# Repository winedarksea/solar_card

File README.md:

# Solar-Powered LED Flashlight Business Card
created by Colin Catlin, 2023

A business card that can also double as a decently powerful, RGB flashlight, complete with solar charging. Built for business, ready for the apocalypse.

Built in KiCAD V6, opens with V7 and possibly later (those haven't been released as of this release).

GPLv3 licensed so that you can freely go and make variations with your own name. Or run around handling out ones with my name while pretending to be me? Please only do the latter if you are very charming and attractive.

I have had this made and assembled by JLCPCB, as you'll notice. Only the back side was assembled by them. 
Additionally there is a PTC reset fuse which is marked with a 0 ohm resistor, size 1812. 
You can use the resistor if you don't want the reset fuse, it isn't necessary but adds a little extra safety.

For that fuse, I chose Bourns MF-MSMF020-2 PTC RESET FUSE 30V 200MA 1812 and hand-assembled it with hot air. It's a relatively big part, easy to solder.

I also hand assembled the solar panel and the LEDs on the front side. Choosing LEDs is fun. I tried to size the pad so that that most 3030 or 2835 LEDs would work. 
I found that it even works with those that have a three part footprint (one of which can safely be connected to return). 

The giant vias are for allowing hot air from the bottom to reach solder paste on the other side for attaching the solar panel. It works. Actually these vias are bigger than really necessary, going down a bit smaller would work well and be more discrete, but not too small, 0.3 mm was definitely too small.

The idea here with three LEDs is that you can choose three different colors, red, green, and blue, and then mix them with potentiometers to make 'any' color. It works! 
But for more flashlight purposes you can just choose the most efficient white-ish colors (for still some fun, choose a low kelvin and high kelvin color mix, so you still can get blue-ish and yellow-ish). I had thought the Samsung ultra efficient LEDs would be best, and they do work well, but for the best flashlight I found the narrowest possible viewing angle made the most impact (since there is no light focusing reflector here like a normal flashlight). One I tried that worked well was the "LED Lighting OSLON® SSL 80 White, Cool 6500K 2.85V 350mA 80° 1212 (3030 Metric)" - the most important part is that 80 degree viewing angle.

The idea here was the undervoltage protection would be afforded by the dropout voltage of the LEDs (they stop working with too little voltage, that's good here). Unfortunately I have found that green LEDs, in particular, can run down to a lower voltage than their datasheet suggests. Check the minimum voltage of LEDs manually if aiming for optimal battery protection.

Please see my blogpost for more details: 
https://syllepsis.live/2023/08/05/the-solar-powered-business-card/

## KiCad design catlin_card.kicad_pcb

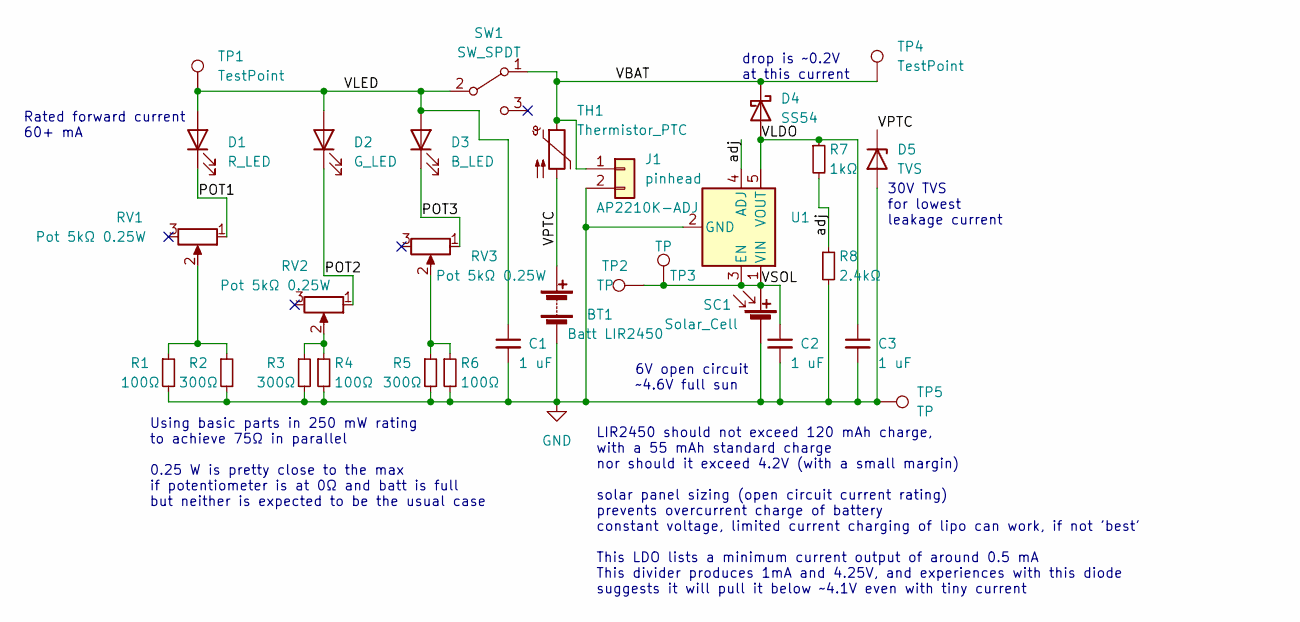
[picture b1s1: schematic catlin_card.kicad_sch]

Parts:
BT1: Batt LIR2450; BatteryHolder_Keystone_3008_1x2450
C1, C2, C3: 1 uF; C_0805_2012Metric_Pad1.18x1.45mm_HandSolder
D1: R_LED; LED_SMD3030
D2: G_LED; LED_SMD3030
D3: B_LED; LED_SMD3030
D4: SS54; D_SMA_Handsoldering
D5: TVS; D_SOD-123
J1: pinhead; PinHeader_1x02_P2.54mm_Vertical
R1, R4, R6: 100Ω; R_1206_3216Metric
R2, R3, R5: 300Ω; R_1206_3216Metric
R7: 1kΩ; R_0805_2012Metric_Pad1.20x1.40mm_HandSolder
R8: 2.4kΩ; R_0805_2012Metric_Pad1.20x1.40mm_HandSolder
RV1, RV2, RV3: Pot 5kΩ 0.25W; Potentiometer_Bourns_3314G_Vertical
SC1: Solar_Cell; R_4020_10251Metric
SW1: SW_SPDT; SW_SPDT_PCM12
TH1: Thermistor_PTC; R_1812_4532Metric_Pad1.30x3.40mm_HandSolder
TP1, TP4: TestPoint; TestPoint_Pad_2.0x2.0mm
TP2, TP5: TP; TestPoint_Pad_4.0x4.0mm
TP3: TP; TestPoint_Pad_1.0x1.0mm
U1: AP2210K-ADJ; SOT-23-5

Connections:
/POT1: D1.1 (K), RV1.1
/POT2: D2.1 (K), RV2.1
/POT3: D3.1 (K), RV3.1
/VBAT: D4.1 (K), J1.1, SW1.1 (A), TH1.1, TP4.1
/VLDO: C3.1, D4.2 (A), R7.1, U1.5 (VOUT)
/VLED: C1.1, D1.2 (A), D2.2 (A), D3.2 (A), SW1.2 (B), TP1.1
/VPTC: BT1.1 (+), D5.1 (K), TH1.2
/VSOL: C2.1, SC1.1 (+), TP2.1, TP3.1, U1.1 (VIN), U1.3 (EN)
/adj: R7.2, R8.1, U1.4 (ADJ)
GND: BT1.2 (-), C1.2, C2.2, C3.2, D5.2 (A), J1.2, R1.2, R2.2, R3.2, R4.2, R5.2, R6.2, R8.2, SC1.2 (-), TP5.1, U1.2 (GND)
unnamed: R1.1, R2.1, RV1.2
unnamed: R3.1, R4.1, RV2.2
unnamed: R5.1, R6.1, RV3.2

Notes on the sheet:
Rated forward current 60+ mA
LIR2450 should not exceed 120 mAh charge, with a 55 mAh standard charge nor should it exceed 4.2V (with a small margin) solar panel sizing (open circuit current rating) prevents overcurrent charge of battery constant voltage, limited current charging of lipo can work, if not 'best' This LDO lists a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
6V open circuit ~4.6V full sun
30V TVS for lowest leakage current
Using basic parts in 250 mW rating to achieve 75Ω in parallel 0.25 W is pretty close to the max if potentiometer is at 0Ω and batt is full but neither is expected to be the usual case
drop is ~0.2V at this current

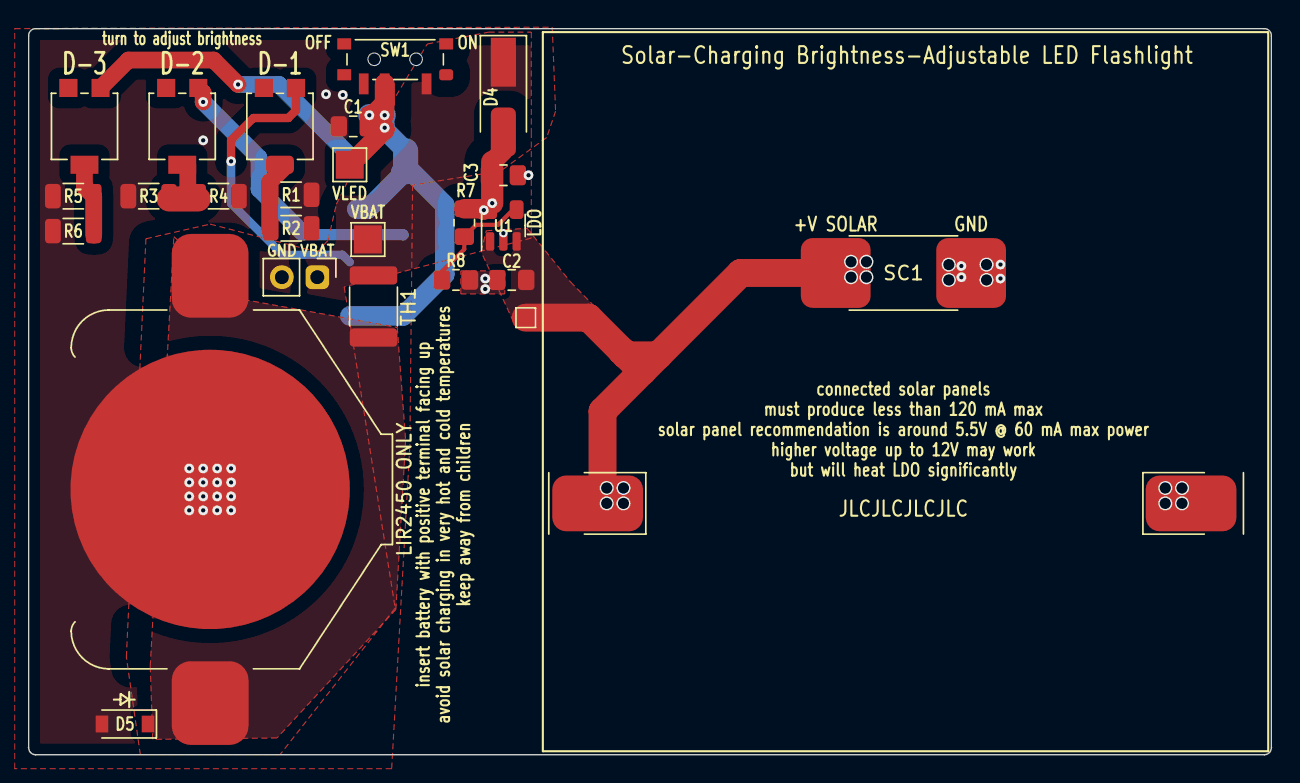
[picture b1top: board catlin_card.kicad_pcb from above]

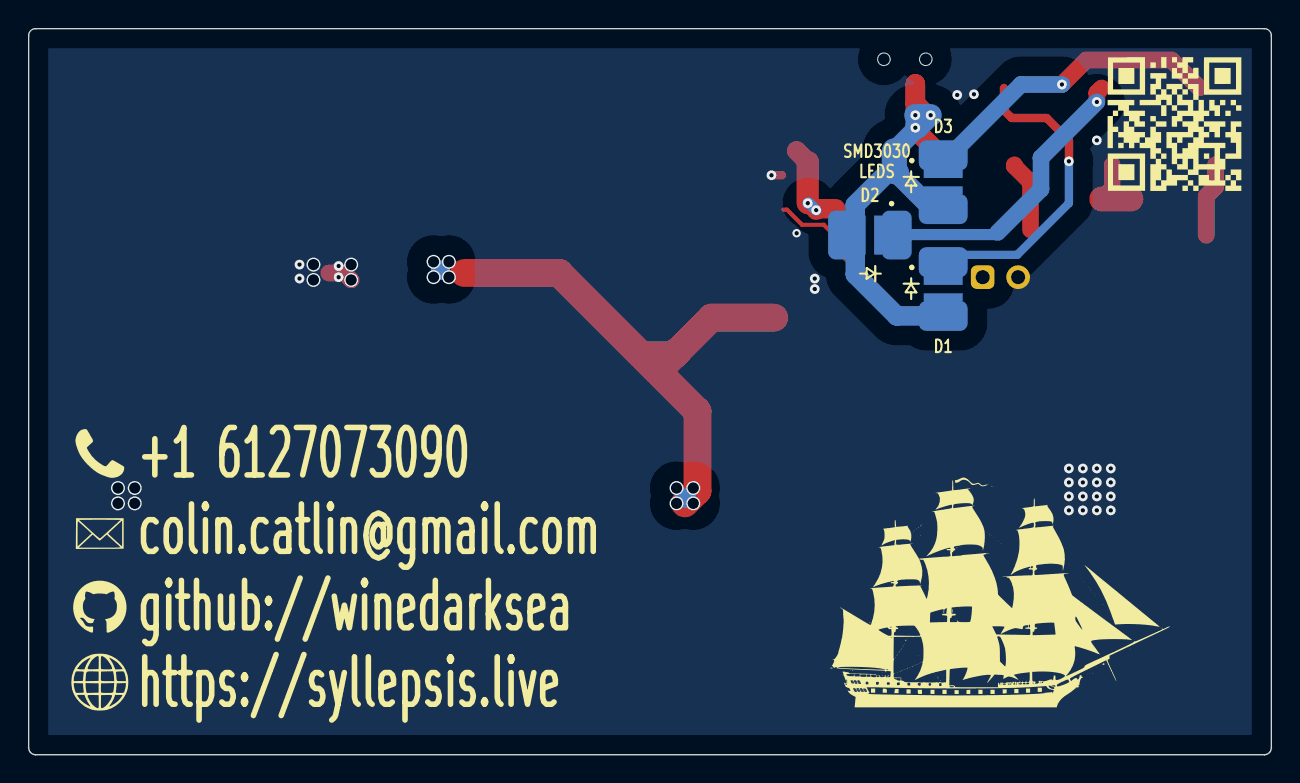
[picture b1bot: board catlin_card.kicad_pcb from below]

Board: 2 copper layers, 89.0 x 52.0 mm, 30 parts (3 on the bottom side), 13 nets.

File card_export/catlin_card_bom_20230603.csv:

Designator,Comment,Footprint,JCLPCB Part #
"BT1,",Batt LIR2450,Battery:BatteryHolder_Keystone_3008_1x2450,C964845
"C1, C2, C3,",1 uF,Capacitor_SMD:C_0805_2012Metric_Pad1.18x1.45mm_HandSolder,C28323
"D1,",R_LED,PowerIC:LED_SMD3030,C1322324
"D2,",G_LED,PowerIC:LED_SMD3030,C1322325
"D3,",B_LED,PowerIC:LED_SMD3030,C440449
"D4,",SS54,Diode_SMD:D_SMA_Handsoldering,C22452
"D5,",TVS,Diode_SMD:D_SOD-123,C2990493
"J1,",pinhead,Connector_PinHeader_2.54mm:PinHeader_1x02_P2.54mm_Vertical,
"R1, R4, R6,",100Ω,Resistor_SMD:R_1206_3216Metric,C17901
"R2, R3, R5,",300Ω,Resistor_SMD:R_1206_3216Metric,C17887
"R7,",1kΩ,Resistor_SMD:R_0805_2012Metric_Pad1.20x1.40mm_HandSolder,C17513
"R8,",2.4kΩ,Resistor_SMD:R_0805_2012Metric_Pad1.20x1.40mm_HandSolder,C17526
"RV1, RV2, RV3,",Pot 5kΩ 0.25W,Potentiometer_SMD:Potentiometer_Bourns_3314G_Vertical,C719180
"SC1,",Solar_Cell,Resistor_SMD:R_4020_10251Metric,SM141K10LV
"SW1,",SW_SPDT,Button_Switch_SMD:SW_SPDT_PCM12,C128955
"TH1,",Thermistor_PTC,Resistor_SMD:R_1812_4532Metric_Pad1.30x3.40mm_HandSolder,
"TP1, TP4,",TestPoint,TestPoint:TestPoint_Pad_2.0x2.0mm,
"TP2, TP5,",TP,TestPoint:TestPoint_Pad_4.0x4.0mm,
"TP3,",TP,TestPoint:TestPoint_Pad_1.0x1.0mm,
"U1,",AP2210K-ADJ,Package_TO_SOT_SMD:SOT-23-5,C507874

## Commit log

2023-08-05 1.0.0
    upload of existing files
